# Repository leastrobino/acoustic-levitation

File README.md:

# Acoustic levitation

An acoustic levitation device designed as a daughterboard for the [DE0-Nano-SoC](http://www.terasic.com.tw/cgi-bin/page/archive.pl?Language=English&CategoryNo=165&No=941) (Terasic Inc.)

The piezoelectric transducers signals generation is written in VHDL. The phases computation and the G-Code interpreter are written in C and run on embedded Linux. The device controls 88 channels at 40 kHz with a phase resolution of π/625.

## Demonstration videos

#### Levitation of a 3 mm EPS particle in hand

#### Up and down movements using G-Code

#### 2 mm EPS particle following a toolpath exported from FlatCAM

Toolpath:

## Bill of materials

| Quantity | Manufacturer           | Part number     |
| :------: | :--------------------- | :-------------- |
| 1        | CUI Inc.               | PJ-102AH        |
| 14       | Maxim Integrated       | MAX17079GTL+    |
| 88       | Murata                 | MA40S4S         |
| 2        | Samtec Inc.            | SSW-120-03-G-D  |
| 8        | TE Connectivity        | 8-215079-8      |
| 8        | TE Connectivity        | 8-215083-8      |
| 176      | TE Connectivity        | 8134-HC-8P2     |
| 1        | Traco Power            | TSR 2-2450      |
| 1        | Vishay Siliconix       | SI3421DV-T1-GE3 |
| 1        | Wurth Electronics Inc. | 61300111121     |
| 1        | Wurth Electronics Inc. | 61300811121     |
| 1        | Wurth Electronics Inc. | 61301011121     |
| 28       | Wurth Electronics Inc. | 885012207072    |

The PCBs were manufactured by [Eurocircuits](https://www.eurocircuits.com) (class 6D).

## License

This project is licensed under the [CERN OHL v1.2](LICENSE).

## References

1. A. Marzo, S. A. Seah, B. W. Drinkwater, D. R. Sahoo, B. Long, and S. Subramanian, *Holographic acoustic elements for manipulation of levitated objects*, Nature Communications 6, 8661, 2015.  
   <https://www.nature.com/articles/ncomms9661>
2. A. Marzo, *GauntLev: A Wearable to Manipulate Free-floating Objects*, Proceedings of the 2016 CHI Conference on Human Factors in Computing Systems (CHI '16), 3277-3281, 2016.  
   <https://dl.acm.org/citation.cfm?id=2858370>
3. A. Marzo, M. Caleap, and B. W. Drinkwater, *Acoustic Virtual Vortices with Tunable Orbital Angular Momentum for Trapping of Mie Particles*, Phys. Rev. Lett. 120, 044301, 2018.  
   <https://journals.aps.org/prl/abstract/10.1103/PhysRevLett.120.044301>
4. A. Künstner, *Lévitation acoustique*, Bachelor thesis, hepia, University of Applied Sciences Western Switzerland (HES-SO), Geneva, Switzerland, 2017.

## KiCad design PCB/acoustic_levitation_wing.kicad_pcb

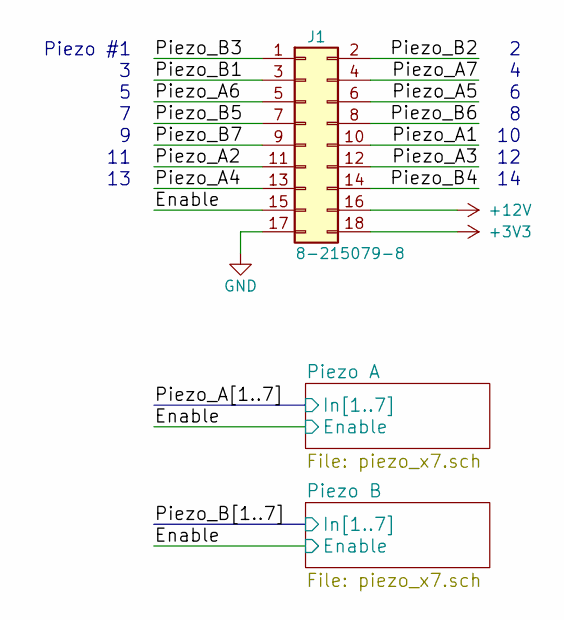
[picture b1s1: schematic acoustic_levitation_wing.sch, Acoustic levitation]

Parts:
J1: 8-215079-8; TE_8-215079-8; ManufacturerPartNumber 8-215079-8

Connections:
+3V3: J1.18; also elsewhere on the board
+12V: J1.16; also elsewhere on the board
/Enable: J1.15; also elsewhere on the board
/Piezo_A1: J1.10; also elsewhere on the board
/Piezo_A2: J1.11; also elsewhere on the board
/Piezo_A3: J1.12; also elsewhere on the board
/Piezo_A4: J1.13; also elsewhere on the board
/Piezo_A5: J1.6; also elsewhere on the board
/Piezo_A6: J1.5; also elsewhere on the board
/Piezo_A7: J1.4; also elsewhere on the board
/Piezo_B1: J1.3; also elsewhere on the board
/Piezo_B2: J1.2; also elsewhere on the board
/Piezo_B3: J1.1; also elsewhere on the board
/Piezo_B4: J1.14; also elsewhere on the board
/Piezo_B5: J1.7; also elsewhere on the board
/Piezo_B6: J1.8; also elsewhere on the board
/Piezo_B7: J1.9; also elsewhere on the board
GND: J1.17; also elsewhere on the board

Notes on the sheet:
Piezo #1

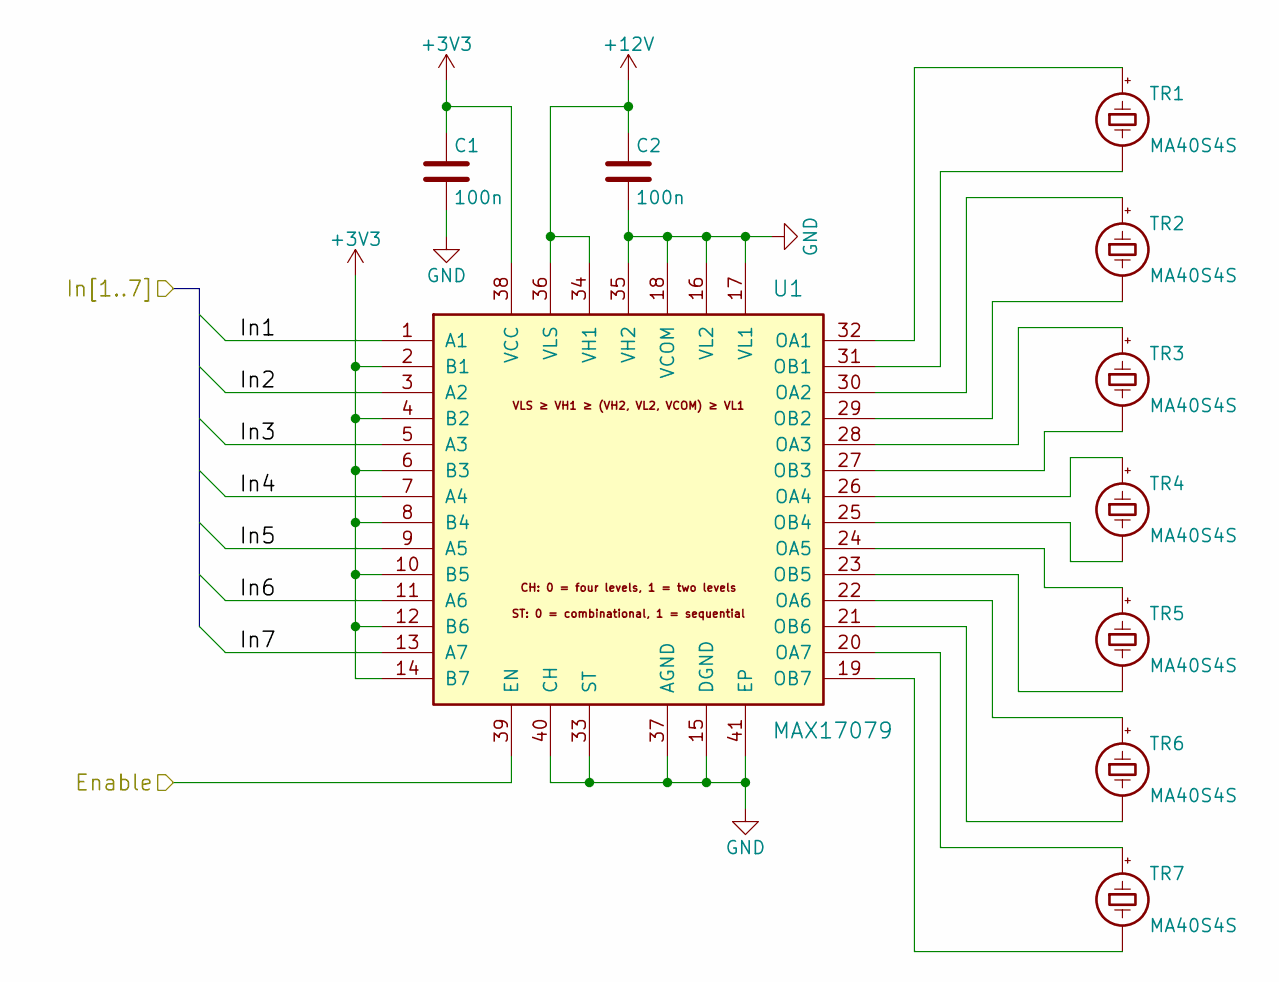
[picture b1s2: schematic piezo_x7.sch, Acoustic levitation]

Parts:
C1, C2: 100n; C_0805_HandSoldering; ManufacturerPartNumber 885012207072
TR1, TR2, TR3, TR4, TR5, TR6, TR7: MA40S4S; Murata_MA40S4S_TE_8134-HC-8P2; ManufacturerPartNumber MA40S4S
U1: MAX17079; QFN-40-1EP_6x6mm_Pitch0.5mm_HandSoldering; ManufacturerPartNumber MAX17079GTL+

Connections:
+3V3: C1.1, U1.2 (B1), U1.4 (B2), U1.6 (B3), U1.8 (B4), U1.10 (B5), U1.12 (B6), U1.14 (B7), U1.38 (VCC); also elsewhere on the board
+12V: C2.1, U1.34 (VH1), U1.36 (VLS); also elsewhere on the board
/Enable: U1.39 (EN); also elsewhere on the board
/Piezo_A1: U1.1 (A1); also elsewhere on the board
/Piezo_A2: U1.3 (A2); also elsewhere on the board
/Piezo_A3: U1.5 (A3); also elsewhere on the board
/Piezo_A4: U1.7 (A4); also elsewhere on the board
/Piezo_A5: U1.9 (A5); also elsewhere on the board
/Piezo_A6: U1.11 (A6); also elsewhere on the board
/Piezo_A7: U1.13 (A7); also elsewhere on the board
GND: C1.2, C2.2, U1.15 (DGND), U1.16 (VL2), U1.17 (VL1), U1.18 (VCOM), U1.33 (ST), U1.35 (VH2), U1.37 (AGND), U1.40 (CH), U1.41 (EP); also elsewhere on the board
unnamed: TR1.1 (-), U1.31 (OB1)
unnamed: TR1.2 (+), U1.32 (OA1)
unnamed: TR2.1 (-), U1.29 (OB2)
unnamed: TR2.2 (+), U1.30 (OA2)
unnamed: TR3.1 (-), U1.27 (OB3)
unnamed: TR3.2 (+), U1.28 (OA3)
unnamed: TR4.1 (-), U1.25 (OB4)
unnamed: TR4.2 (+), U1.26 (OA4)
unnamed: TR5.1 (-), U1.23 (OB5)
unnamed: TR5.2 (+), U1.24 (OA5)
unnamed: TR6.1 (-), U1.21 (OB6)
unnamed: TR6.2 (+), U1.22 (OA6)
unnamed: TR7.1 (-), U1.19 (OB7)
unnamed: TR7.2 (+), U1.20 (OA7)

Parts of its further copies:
C3, C4: 100n; C_0805_HandSoldering; ManufacturerPartNumber 885012207072
TR8, TR9, TR10, TR11, TR12, TR13, TR14: MA40S4S; Murata_MA40S4S_TE_8134-HC-8P2; ManufacturerPartNumber MA40S4S
U2: MAX17079; QFN-40-1EP_6x6mm_Pitch0.5mm_HandSoldering; ManufacturerPartNumber MAX17079GTL+

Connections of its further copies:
+3V3: C3.1, U2.2 (B1), U2.4 (B2), U2.6 (B3), U2.8 (B4), U2.10 (B5), U2.12 (B6), U2.14 (B7), U2.38 (VCC); also elsewhere on the board
+12V: C4.1, U2.34 (VH1), U2.36 (VLS); also elsewhere on the board
/Enable: U2.39 (EN); also elsewhere on the board
/Piezo_B1: U2.1 (A1); also elsewhere on the board
/Piezo_B2: U2.3 (A2); also elsewhere on the board
/Piezo_B3: U2.5 (A3); also elsewhere on the board
/Piezo_B4: U2.7 (A4); also elsewhere on the board
/Piezo_B5: U2.9 (A5); also elsewhere on the board
/Piezo_B6: U2.11 (A6); also elsewhere on the board
/Piezo_B7: U2.13 (A7); also elsewhere on the board
GND: C3.2, C4.2, U2.15 (DGND), U2.16 (VL2), U2.17 (VL1), U2.18 (VCOM), U2.33 (ST), U2.35 (VH2), U2.37 (AGND), U2.40 (CH), U2.41 (EP); also elsewhere on the board
unnamed: TR8.1 (-), U2.31 (OB1)
unnamed: TR8.2 (+), U2.32 (OA1)
unnamed: TR9.1 (-), U2.29 (OB2)
unnamed: TR9.2 (+), U2.30 (OA2)
unnamed: TR10.1 (-), U2.27 (OB3)
unnamed: TR10.2 (+), U2.28 (OA3)
unnamed: TR11.1 (-), U2.25 (OB4)
unnamed: TR11.2 (+), U2.26 (OA4)
unnamed: TR12.1 (-), U2.23 (OB5)
unnamed: TR12.2 (+), U2.24 (OA5)
unnamed: TR13.1 (-), U2.21 (OB6)
unnamed: TR13.2 (+), U2.22 (OA6)
unnamed: TR14.1 (-), U2.19 (OB7)
unnamed: TR14.2 (+), U2.20 (OA7)

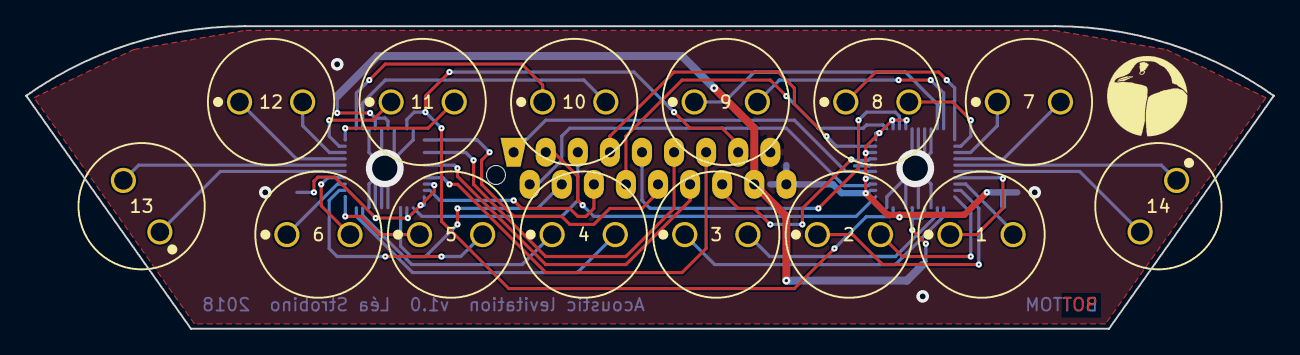
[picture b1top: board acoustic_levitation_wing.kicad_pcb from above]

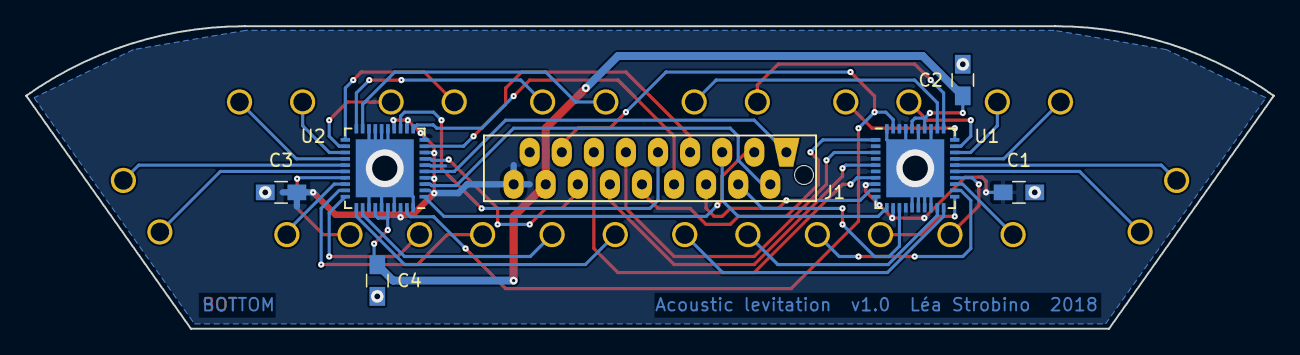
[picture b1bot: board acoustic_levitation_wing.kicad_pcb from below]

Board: 2 copper layers, 98.8 x 24.0 mm, 21 parts (7 on the bottom side), 46 nets.

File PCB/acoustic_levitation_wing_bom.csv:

% Source: /Users/Lea/Documents/Acoustic levitation/PCB/acoustic_levitation_wing.sch
"% Date: Saturday, 03 November 2018 at 16:48:45"
% Component count: 21
Reference,Quantity,Value,Footprint,Manufacturer,Manufacturer part number,Supplier 1,Supplier part number 1,Supplier 2,Supplier part number 2
"C1, C2, C3, C4",4,100n,C_0805_HandSoldering,Wurth Electronics Inc.,885012207072,Digi-Key,732-8061-1-ND,,
J1,1,8-215079-8,TE_8-215079-8,TE Connectivity AMP Connectors,8-215079-8,Digi-Key,A99466CT-ND,,
"TR1, TR2, TR3, TR4, TR5, TR6, TR7, TR8, TR9, TR10, TR11, TR12, TR13, TR14",14,MA40S4S,Murata_MA40S4S_TE_8134-HC-8P2,Murata,MA40S4S,Digi-Key,490-7707-ND,,
"U1, U2",2,MAX17079,QFN-40-1EP_6x6mm_Pitch0.5mm_HandSoldering,Maxim Integrated,MAX17079GTL+,Digi-Key,MAX17079GTL+-ND,,

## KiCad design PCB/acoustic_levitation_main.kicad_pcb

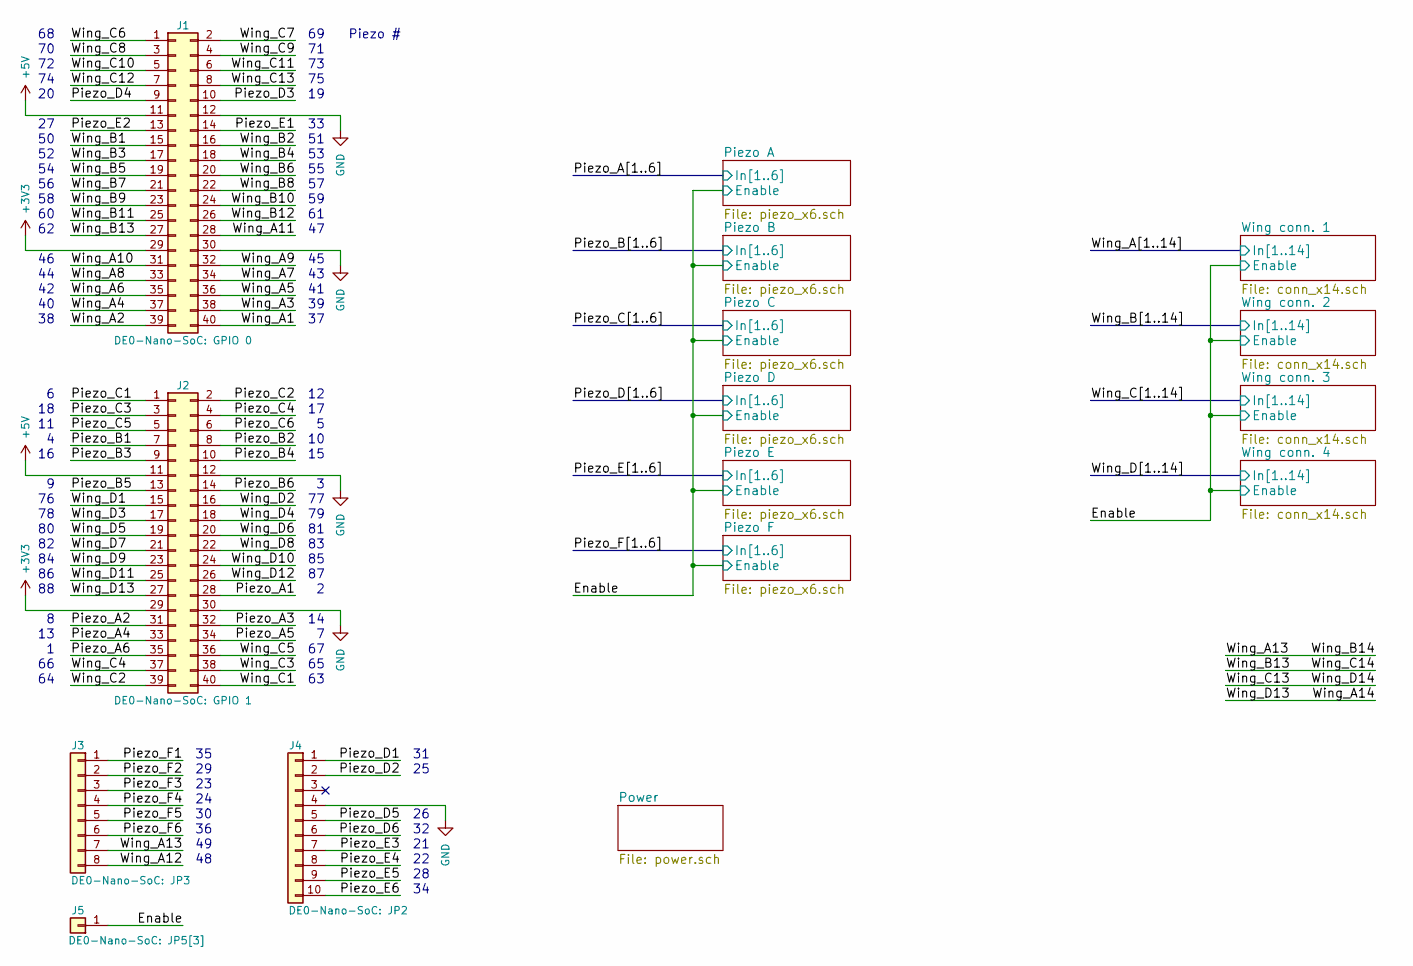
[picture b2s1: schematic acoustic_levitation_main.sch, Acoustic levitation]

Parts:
J1: DE0-Nano-SoC: GPIO 0; Socket_Strip_Straight_2x20_Pitch2.54mm; ManufacturerPartNumber SSW-120-03-G-D
J2: DE0-Nano-SoC: GPIO 1; Socket_Strip_Straight_2x20_Pitch2.54mm; ManufacturerPartNumber SSW-120-03-G-D
J3: DE0-Nano-SoC: JP3; Pin_Header_Straight_1x08_Pitch2.54mm; ManufacturerPartNumber 61300811121
J4: DE0-Nano-SoC: JP2; Pin_Header_Straight_1x10_Pitch2.54mm; ManufacturerPartNumber 61301011121
J5: DE0-Nano-SoC: JP5[3]; Pin_Header_Straight_1x01_Pitch2.54mm; ManufacturerPartNumber 61300111121

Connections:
+3V3: J1.29, J2.29; also elsewhere on the board
+5V: J1.11, J2.11; also elsewhere on the board
/Enable: J5.1; also elsewhere on the board
/Piezo_A1: J2.28; also elsewhere on the board
/Piezo_A2: J2.31; also elsewhere on the board
/Piezo_A3: J2.32; also elsewhere on the board
/Piezo_A4: J2.33; also elsewhere on the board
/Piezo_A5: J2.34; also elsewhere on the board
/Piezo_A6: J2.35; also elsewhere on the board
/Piezo_B1: J2.7; also elsewhere on the board
/Piezo_B2: J2.8; also elsewhere on the board
/Piezo_B3: J2.9; also elsewhere on the board
/Piezo_B4: J2.10; also elsewhere on the board
/Piezo_B5: J2.13; also elsewhere on the board
/Piezo_B6: J2.14; also elsewhere on the board
/Piezo_C1: J2.1; also elsewhere on the board
/Piezo_C2: J2.2; also elsewhere on the board
/Piezo_C3: J2.3; also elsewhere on the board
/Piezo_C4: J2.4; also elsewhere on the board
/Piezo_C5: J2.5; also elsewhere on the board
/Piezo_C6: J2.6; also elsewhere on the board
/Piezo_D1: J4.1; also elsewhere on the board
/Piezo_D2: J4.2; also elsewhere on the board
/Piezo_D3: J1.10; also elsewhere on the board
/Piezo_D4: J1.9; also elsewhere on the board
/Piezo_D5: J4.5; also elsewhere on the board
/Piezo_D6: J4.6; also elsewhere on the board
/Piezo_E1: J1.14; also elsewhere on the board
/Piezo_E2: J1.13; also elsewhere on the board
/Piezo_E3: J4.7; also elsewhere on the board
/Piezo_E4: J4.8; also elsewhere on the board
/Piezo_E5: J4.9; also elsewhere on the board
/Piezo_E6: J4.10; also elsewhere on the board
/Piezo_F1: J3.1; also elsewhere on the board
/Piezo_F2: J3.2; also elsewhere on the board
/Piezo_F3: J3.3; also elsewhere on the board
/Piezo_F4: J3.4; also elsewhere on the board
/Piezo_F5: J3.5; also elsewhere on the board
/Piezo_F6: J3.6; also elsewhere on the board
/Wing_A1: J1.40; also elsewhere on the board
/Wing_A2: J1.39; also elsewhere on the board
/Wing_A3: J1.38; also elsewhere on the board
/Wing_A4: J1.37; also elsewhere on the board
/Wing_A5: J1.36; also elsewhere on the board
/Wing_A6: J1.35; also elsewhere on the board
/Wing_A7: J1.34; also elsewhere on the board
/Wing_A8: J1.33; also elsewhere on the board
/Wing_A9: J1.32; also elsewhere on the board
/Wing_A10: J1.31; also elsewhere on the board
/Wing_A11: J1.28; also elsewhere on the board
/Wing_A12: J3.8; also elsewhere on the board
/Wing_A13: J3.7; also elsewhere on the board
/Wing_A14: J2.27; also elsewhere on the board
/Wing_B1: J1.15; also elsewhere on the board
/Wing_B2: J1.16; also elsewhere on the board
/Wing_B3: J1.17; also elsewhere on the board
/Wing_B4: J1.18; also elsewhere on the board
/Wing_B5: J1.19; also elsewhere on the board
/Wing_B6: J1.20; also elsewhere on the board
/Wing_B7: J1.21; also elsewhere on the board
/Wing_B8: J1.22; also elsewhere on the board
/Wing_B9: J1.23; also elsewhere on the board
/Wing_B10: J1.24; also elsewhere on the board
/Wing_B11: J1.25; also elsewhere on the board
/Wing_B12: J1.26; also elsewhere on the board
/Wing_B13: J1.27; also elsewhere on the board
/Wing_C1: J2.40; also elsewhere on the board
/Wing_C2: J2.39; also elsewhere on the board
/Wing_C3: J2.38; also elsewhere on the board
/Wing_C4: J2.37; also elsewhere on the board
/Wing_C5: J2.36; also elsewhere on the board
/Wing_C6: J1.1; also elsewhere on the board
/Wing_C7: J1.2; also elsewhere on the board
/Wing_C8: J1.3; also elsewhere on the board
/Wing_C9: J1.4; also elsewhere on the board
/Wing_C10: J1.5; also elsewhere on the board
/Wing_C11: J1.6; also elsewhere on the board
/Wing_C12: J1.7; also elsewhere on the board
/Wing_C13: J1.8; also elsewhere on the board
/Wing_D1: J2.15; also elsewhere on the board
/Wing_D2: J2.16; also elsewhere on the board
/Wing_D3: J2.17; also elsewhere on the board
/Wing_D4: J2.18; also elsewhere on the board
/Wing_D5: J2.19; also elsewhere on the board
/Wing_D6: J2.20; also elsewhere on the board
/Wing_D7: J2.21; also elsewhere on the board
/Wing_D8: J2.22; also elsewhere on the board
/Wing_D9: J2.23; also elsewhere on the board
/Wing_D10: J2.24; also elsewhere on the board
/Wing_D11: J2.25; also elsewhere on the board
/Wing_D12: J2.26; also elsewhere on the board
GND: J1.12, J1.30, J2.12, J2.30, J4.4; also elsewhere on the board

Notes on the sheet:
Piezo #

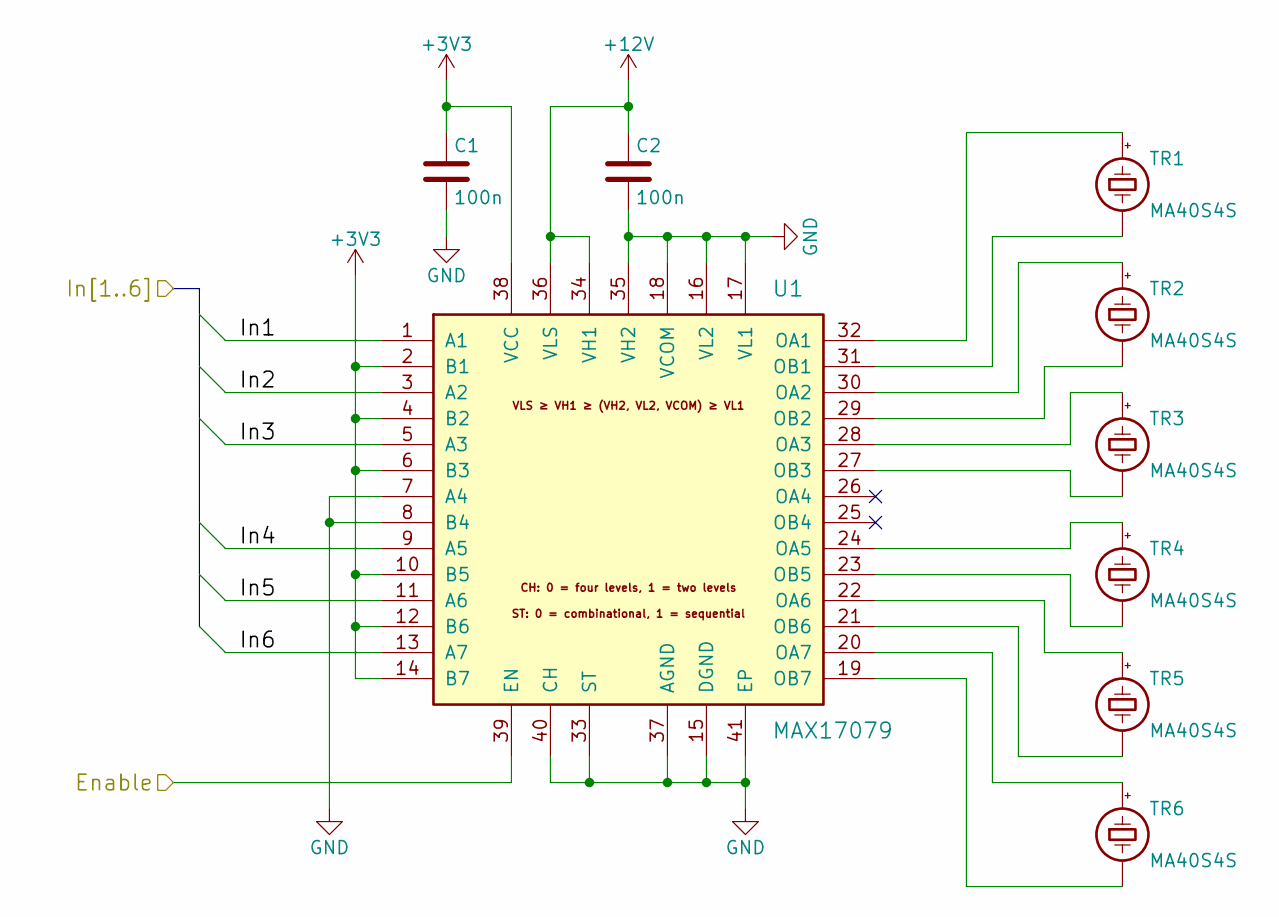
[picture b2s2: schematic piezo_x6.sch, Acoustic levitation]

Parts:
C1, C2: 100n; C_0805_HandSoldering; ManufacturerPartNumber 885012207072
TR1, TR2, TR3, TR4, TR5, TR6: MA40S4S; Murata_MA40S4S_TE_8134-HC-8P2; ManufacturerPartNumber MA40S4S
U1: MAX17079; QFN-40-1EP_6x6mm_Pitch0.5mm_HandSoldering; ManufacturerPartNumber MAX17079GTL+

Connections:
+3V3: C1.1, U1.2 (B1), U1.4 (B2), U1.6 (B3), U1.10 (B5), U1.12 (B6), U1.14 (B7), U1.38 (VCC); also elsewhere on the board
+12V: C2.1, U1.34 (VH1), U1.36 (VLS); also elsewhere on the board
/Enable: U1.39 (EN); also elsewhere on the board
/Piezo_A1: U1.1 (A1); also elsewhere on the board
/Piezo_A2: U1.3 (A2); also elsewhere on the board
/Piezo_A3: U1.5 (A3); also elsewhere on the board
/Piezo_A4: U1.9 (A5); also elsewhere on the board
/Piezo_A5: U1.11 (A6); also elsewhere on the board
/Piezo_A6: U1.13 (A7); also elsewhere on the board
GND: C1.2, C2.2, U1.7 (A4), U1.8 (B4), U1.15 (DGND), U1.16 (VL2), U1.17 (VL1), U1.18 (VCOM), U1.33 (ST), U1.35 (VH2), U1.37 (AGND), U1.40 (CH), U1.41 (EP); also elsewhere on the board
unnamed: TR1.1 (-), U1.31 (OB1)
unnamed: TR1.2 (+), U1.32 (OA1)
unnamed: TR2.1 (-), U1.29 (OB2)
unnamed: TR2.2 (+), U1.30 (OA2)
unnamed: TR3.1 (-), U1.27 (OB3)
unnamed: TR3.2 (+), U1.28 (OA3)
unnamed: TR4.1 (-), U1.23 (OB5)
unnamed: TR4.2 (+), U1.24 (OA5)
unnamed: TR5.1 (-), U1.21 (OB6)
unnamed: TR5.2 (+), U1.22 (OA6)
unnamed: TR6.1 (-), U1.19 (OB7)
unnamed: TR6.2 (+), U1.20 (OA7)

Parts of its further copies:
C3, C4, C5, C6, C7, C8, C9, C10, C11, C12: 100n; C_0805_HandSoldering; ManufacturerPartNumber 885012207072
TR7, TR8, TR9, TR10, TR11, TR12, TR13, TR14, TR15, TR16, TR17, TR18, TR19, TR20, TR21, TR22, TR23, TR24, TR25, TR26, TR27, TR28, TR29, TR30, TR31, TR32, TR33, TR34, TR35, TR36: MA40S4S; Murata_MA40S4S_TE_8134-HC-8P2; ManufacturerPartNumber MA40S4S
U2, U3, U4, U5, U6: MAX17079; QFN-40-1EP_6x6mm_Pitch0.5mm_HandSoldering; ManufacturerPartNumber MAX17079GTL+

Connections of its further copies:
+3V3: C3.1, C5.1, C7.1, C9.1, C11.1, U2.2 (B1), U2.4 (B2), U2.6 (B3), U2.10 (B5), U2.12 (B6), U2.14 (B7), U2.38 (VCC), U3.2 (B1), U3.4 (B2), U3.6 (B3), U3.10 (B5), U3.12 (B6), U3.14 (B7), U3.38 (VCC), U4.2 (B1), U4.4 (B2), U4.6 (B3), U4.10 (B5), U4.12 (B6), U4.14 (B7), U4.38 (VCC), U5.2 (B1), U5.4 (B2), U5.6 (B3), U5.10 (B5), U5.12 (B6), U5.14 (B7), U5.38 (VCC), U6.2 (B1), U6.4 (B2), U6.6 (B3), U6.10 (B5), U6.12 (B6), U6.14 (B7), U6.38 (VCC); also elsewhere on the board
+12V: C4.1, C6.1, C8.1, C10.1, C12.1, U2.34 (VH1), U2.36 (VLS), U3.34 (VH1), U3.36 (VLS), U4.34 (VH1), U4.36 (VLS), U5.34 (VH1), U5.36 (VLS), U6.34 (VH1), U6.36 (VLS); also elsewhere on the board
/Enable: U2.39 (EN), U3.39 (EN), U4.39 (EN), U5.39 (EN), U6.39 (EN); also elsewhere on the board
/Piezo_B1: U2.1 (A1); also elsewhere on the board
/Piezo_B2: U2.3 (A2); also elsewhere on the board
/Piezo_B3: U2.5 (A3); also elsewhere on the board
/Piezo_B4: U2.9 (A5); also elsewhere on the board
/Piezo_B5: U2.11 (A6); also elsewhere on the board
/Piezo_B6: U2.13 (A7); also elsewhere on the board
/Piezo_C1: U3.1 (A1); also elsewhere on the board
/Piezo_C2: U3.3 (A2); also elsewhere on the board
/Piezo_C3: U3.5 (A3); also elsewhere on the board
/Piezo_C4: U3.9 (A5); also elsewhere on the board
/Piezo_C5: U3.11 (A6); also elsewhere on the board
/Piezo_C6: U3.13 (A7); also elsewhere on the board
/Piezo_D1: U4.1 (A1); also elsewhere on the board
/Piezo_D2: U4.3 (A2); also elsewhere on the board
/Piezo_D3: U4.5 (A3); also elsewhere on the board
/Piezo_D4: U4.9 (A5); also elsewhere on the board
/Piezo_D5: U4.11 (A6); also elsewhere on the board
/Piezo_D6: U4.13 (A7); also elsewhere on the board
/Piezo_E1: U5.1 (A1); also elsewhere on the board
/Piezo_E2: U5.3 (A2); also elsewhere on the board
/Piezo_E3: U5.5 (A3); also elsewhere on the board
/Piezo_E4: U5.9 (A5); also elsewhere on the board
/Piezo_E5: U5.11 (A6); also elsewhere on the board
/Piezo_E6: U5.13 (A7); also elsewhere on the board
/Piezo_F1: U6.1 (A1); also elsewhere on the board
/Piezo_F2: U6.3 (A2); also elsewhere on the board
/Piezo_F3: U6.5 (A3); also elsewhere on the board
/Piezo_F4: U6.9 (A5); also elsewhere on the board
/Piezo_F5: U6.11 (A6); also elsewhere on the board
/Piezo_F6: U6.13 (A7); also elsewhere on the board
GND: C3.2, C4.2, C5.2, C6.2, C7.2, C8.2, C9.2, C10.2, C11.2, C12.2, U2.7 (A4), U2.8 (B4), U2.15 (DGND), U2.16 (VL2), U2.17 (VL1), U2.18 (VCOM), U2.33 (ST), U2.35 (VH2), U2.37 (AGND), U2.40 (CH), U2.41 (EP), U3.7 (A4), U3.8 (B4), U3.15 (DGND), U3.16 (VL2), U3.17 (VL1), U3.18 (VCOM), U3.33 (ST), U3.35 (VH2), U3.37 (AGND), U3.40 (CH), U3.41 (EP), U4.7 (A4), U4.8 (B4), U4.15 (DGND), U4.16 (VL2), U4.17 (VL1), U4.18 (VCOM), U4.33 (ST), U4.35 (VH2), U4.37 (AGND), U4.40 (CH), U4.41 (EP), U5.7 (A4), U5.8 (B4), U5.15 (DGND), U5.16 (VL2), U5.17 (VL1), U5.18 (VCOM), U5.33 (ST), U5.35 (VH2), U5.37 (AGND), U5.40 (CH), U5.41 (EP), U6.7 (A4), U6.8 (B4), U6.15 (DGND), U6.16 (VL2), U6.17 (VL1), U6.18 (VCOM), U6.33 (ST), U6.35 (VH2), U6.37 (AGND), U6.40 (CH), U6.41 (EP); also elsewhere on the board
unnamed: TR7.1 (-), U2.31 (OB1)
unnamed: TR7.2 (+), U2.32 (OA1)
unnamed: TR8.1 (-), U2.29 (OB2)
unnamed: TR8.2 (+), U2.30 (OA2)
unnamed: TR9.1 (-), U2.27 (OB3)
unnamed: TR9.2 (+), U2.28 (OA3)
unnamed: TR10.1 (-), U2.23 (OB5)
unnamed: TR10.2 (+), U2.24 (OA5)
unnamed: TR11.1 (-), U2.21 (OB6)
unnamed: TR11.2 (+), U2.22 (OA6)
unnamed: TR12.1 (-), U2.19 (OB7)
unnamed: TR12.2 (+), U2.20 (OA7)
unnamed: TR13.1 (-), U3.31 (OB1)
unnamed: TR13.2 (+), U3.32 (OA1)
unnamed: TR14.1 (-), U3.29 (OB2)
unnamed: TR14.2 (+), U3.30 (OA2)
unnamed: TR15.1 (-), U3.27 (OB3)
unnamed: TR15.2 (+), U3.28 (OA3)
unnamed: TR16.1 (-), U3.23 (OB5)
unnamed: TR16.2 (+), U3.24 (OA5)
unnamed: TR17.1 (-), U3.21 (OB6)
unnamed: TR17.2 (+), U3.22 (OA6)
unnamed: TR18.1 (-), U3.19 (OB7)
unnamed: TR18.2 (+), U3.20 (OA7)
unnamed: TR19.1 (-), U4.31 (OB1)
unnamed: TR19.2 (+), U4.32 (OA1)
unnamed: TR20.1 (-), U4.29 (OB2)
unnamed: TR20.2 (+), U4.30 (OA2)
unnamed: TR21.1 (-), U4.27 (OB3)
unnamed: TR21.2 (+), U4.28 (OA3)
unnamed: TR22.1 (-), U4.23 (OB5)
unnamed: TR22.2 (+), U4.24 (OA5)
unnamed: TR23.1 (-), U4.21 (OB6)
unnamed: TR23.2 (+), U4.22 (OA6)
unnamed: TR24.1 (-), U4.19 (OB7)
unnamed: TR24.2 (+), U4.20 (OA7)
unnamed: TR25.1 (-), U5.31 (OB1)
unnamed: TR25.2 (+), U5.32 (OA1)
unnamed: TR26.1 (-), U5.29 (OB2)
unnamed: TR26.2 (+), U5.30 (OA2)
unnamed: TR27.1 (-), U5.27 (OB3)
unnamed: TR27.2 (+), U5.28 (OA3)
unnamed: TR28.1 (-), U5.23 (OB5)
unnamed: TR28.2 (+), U5.24 (OA5)
unnamed: TR29.1 (-), U5.21 (OB6)
unnamed: TR29.2 (+), U5.22 (OA6)
unnamed: TR30.1 (-), U5.19 (OB7)
unnamed: TR30.2 (+), U5.20 (OA7)
unnamed: TR31.1 (-), U6.31 (OB1)
unnamed: TR31.2 (+), U6.32 (OA1)
unnamed: TR32.1 (-), U6.29 (OB2)
unnamed: TR32.2 (+), U6.30 (OA2)
unnamed: TR33.1 (-), U6.27 (OB3)
unnamed: TR33.2 (+), U6.28 (OA3)
unnamed: TR34.1 (-), U6.23 (OB5)
unnamed: TR34.2 (+), U6.24 (OA5)
unnamed: TR35.1 (-), U6.21 (OB6)
unnamed: TR35.2 (+), U6.22 (OA6)
unnamed: TR36.1 (-), U6.19 (OB7)
unnamed: TR36.2 (+), U6.20 (OA7)

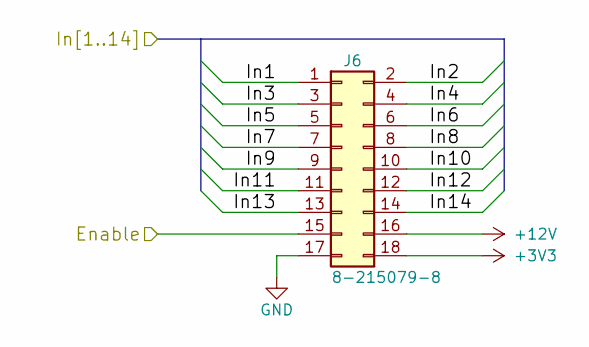
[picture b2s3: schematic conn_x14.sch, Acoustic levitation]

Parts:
J6: 8-215079-8; TE_8-215079-8; ManufacturerPartNumber 8-215079-8

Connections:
+3V3: J6.18; also elsewhere on the board
+12V: J6.16; also elsewhere on the board
/Enable: J6.15; also elsewhere on the board
/Wing_A1: J6.1; also elsewhere on the board
/Wing_A2: J6.2; also elsewhere on the board
/Wing_A3: J6.3; also elsewhere on the board
/Wing_A4: J6.4; also elsewhere on the board
/Wing_A5: J6.5; also elsewhere on the board
/Wing_A6: J6.6; also elsewhere on the board
/Wing_A7: J6.7; also elsewhere on the board
/Wing_A8: J6.8; also elsewhere on the board
/Wing_A9: J6.9; also elsewhere on the board
/Wing_A10: J6.10; also elsewhere on the board
/Wing_A11: J6.11; also elsewhere on the board
/Wing_A12: J6.12; also elsewhere on the board
/Wing_A13: J6.13; also elsewhere on the board
/Wing_A14: J6.14; also elsewhere on the board
GND: J6.17; also elsewhere on the board

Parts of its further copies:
J7, J8, J9: 8-215079-8; TE_8-215079-8; ManufacturerPartNumber 8-215079-8

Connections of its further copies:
+3V3: J7.18, J8.18, J9.18; also elsewhere on the board
+12V: J7.16, J8.16, J9.16; also elsewhere on the board
/Enable: J7.15, J8.15, J9.15; also elsewhere on the board
/Wing_A13: J7.14; also elsewhere on the board
/Wing_A14: J9.13; also elsewhere on the board
/Wing_B1: J7.1; also elsewhere on the board
/Wing_B2: J7.2; also elsewhere on the board
/Wing_B3: J7.3; also elsewhere on the board
/Wing_B4: J7.4; also elsewhere on the board
/Wing_B5: J7.5; also elsewhere on the board
/Wing_B6: J7.6; also elsewhere on the board
/Wing_B7: J7.7; also elsewhere on the board
/Wing_B8: J7.8; also elsewhere on the board
/Wing_B9: J7.9; also elsewhere on the board
/Wing_B10: J7.10; also elsewhere on the board
/Wing_B11: J7.11; also elsewhere on the board
/Wing_B12: J7.12; also elsewhere on the board
/Wing_B13: J7.13, J8.14; also elsewhere on the board
/Wing_C1: J8.1; also elsewhere on the board
/Wing_C2: J8.2; also elsewhere on the board
/Wing_C3: J8.3; also elsewhere on the board
/Wing_C4: J8.4; also elsewhere on the board
/Wing_C5: J8.5; also elsewhere on the board
/Wing_C6: J8.6; also elsewhere on the board
/Wing_C7: J8.7; also elsewhere on the board
/Wing_C8: J8.8; also elsewhere on the board
/Wing_C9: J8.9; also elsewhere on the board
/Wing_C10: J8.10; also elsewhere on the board
/Wing_C11: J8.11; also elsewhere on the board
/Wing_C12: J8.12; also elsewhere on the board
/Wing_C13: J8.13, J9.14; also elsewhere on the board
/Wing_D1: J9.1; also elsewhere on the board
/Wing_D2: J9.2; also elsewhere on the board
/Wing_D3: J9.3; also elsewhere on the board
/Wing_D4: J9.4; also elsewhere on the board
/Wing_D5: J9.5; also elsewhere on the board
/Wing_D6: J9.6; also elsewhere on the board
/Wing_D7: J9.7; also elsewhere on the board
/Wing_D8: J9.8; also elsewhere on the board
/Wing_D9: J9.9; also elsewhere on the board
/Wing_D10: J9.10; also elsewhere on the board
/Wing_D11: J9.11; also elsewhere on the board
/Wing_D12: J9.12; also elsewhere on the board
GND: J7.17, J8.17, J9.17; also elsewhere on the board

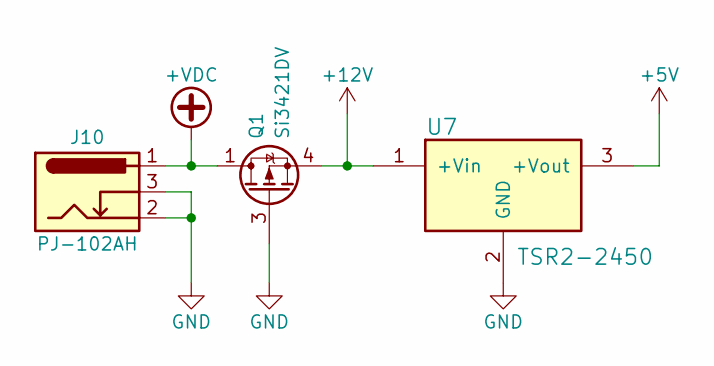
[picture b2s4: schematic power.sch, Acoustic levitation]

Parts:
J10: PJ-102AH; CUI_PJ-102AH; ManufacturerPartNumber PJ-102AH
Q1: Si3421DV; TSOP-6_2.9x1.5mm_Pitch0.95mm; ManufacturerPartNumber SI3421DV-T1-GE3
U7: TSR2-2450; Traco_TSR2; ManufacturerPartNumber TSR 2-2450

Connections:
+5V: U7.3 (+Vout); also elsewhere on the board
+12V: Q1.4 (S), U7.1 (+Vin); also elsewhere on the board
+VDC: J10.1, Q1.1 (D), Q1.2 (D), Q1.5 (D), Q1.6 (D)
GND: J10.2, J10.3, Q1.3 (G), U7.2 (GND); also elsewhere on the board

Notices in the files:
PCB/acoustic_levitation_main.kicad_pcb:
License: CERN OHL v1.2
